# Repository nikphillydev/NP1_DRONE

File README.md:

# NP1 DRONE
I am attempting to build a quadcopter from scratch, both the PCB hardware (using KiCAD) and software (C/C++ on STM32).

I am a computer software engineering student at the University of Alberta. I started this project in early 2024 to push myself with embedded systems. Since its inception, I have learned a ton about PCB design and FreeRTOS firmware on STM32 microcontrollers. 

Everything I make in this project is from scratch. The STM32-based circuit boards are designed with KiCAD and ordered from JLCPCB with assembly. I am using FreeRTOS for the software because of its scalability in complex embedded projects. I have written all the device drivers from scratch, and wholly designed the multi-threaded architecture for each of the drone's sub-systems.

Each sub-system presents its own set of challenges. As an overview, there are 3 sub-systems of the NP1 Drone:
```
                     (Over-The-Air Messaging)                               (CANBUS)
[RC CONTROLLER]   <---------------------------->  [Flight Controller]   <--------------->  [Electronic Speed Controller] x4
```
#### 1. Flight Controller Overview
The Flight Controller (FCC) is a custom PCB design whose software runs the control system for the drone. In order to achieve this, it must 1) receive pilot input from the RC Controller, and 2) estimate its attitude and heading (roll, pitch, yaw). These inputs enter the onboard PID controller in order to calculate the necessary motor commands to send to the Electronic Speed Controllers (ESCs).

The FCC is equipped with a multitude of sensors, namely an IMU, magnetometer, barometer, optical flow sensor, and range finder. It performs sensor fusion through the use of an Extended Kalman Filter (EKF) and a few other custom algorithms. When it receives Over-The-Air (OTA) messages from the RC Controller, it monitors for a HEARTBEAT signal to detect LOSS-OF-LINK and perform flight termination. The control system interprets pilot input and sets the target roll, pitch, and yaw accordingly depending on flight mode (various flight modes still WIP).

<p align="center">
  <br>
  <sub><b>Figure 1:</b> The Flight Controller (FCC) sitting on a Lego frame. The USB powers the board and enables logging to my laptop; jumper wires connect the external range finder and optical flow sensor; the green and yellow twisted pair connect to the ESCs using CANBUS.</sub>
</p>

#### 2. RC Controller Overview
The RC Controller is simple: receive pilot input from various joysticks and buttons and send those values Over-The-Air (OTA) to the FCC. A custom OTA messaging protocol (modelled after MAVLINK) has been developed to facilitate this communication. The physical inputs of the RC Controller are fairly WIP right now. Currently, its a breadboard with push-buttons and a potentiometer, (hopefully) soon it will be a PS4 controller.

<p align="center">
  <br>
  <sub><b>Figure 2:</b> The RC Controller, in its current state. Spare hardware is used to capture pilot input.</sub>
</p>

#### 3. Electronic Speed Controller Overview
The Electronic Speed Controller (ESC) requires a strong understanding of Brushless DC (BLDC) motor control. The custom PCB design and software are designed around the (sensorless) 6-Step Trapezoidal control method, where a Back Electromotive Force (BEMF) measurement from the floating motor phase is measured in order to know when to switch the commutation to the next step. In order to perform proper closed-loop control in this method, the motor must be spinning fast enough to generate a sufficient BEMF. I designed the ESC to operate in a software defined state-machine. Here are the states:
1. STAND-BY: ESC is not commanding a rotation of the motor.
2. ARMING: Align-and-Go Step. ESC commands an open-loop ramp up of the motor to obtain sufficient BEMF measurements. Lasts for about 0.8 sec.
3. ARMED: ESC is commanding true closed-loop, 6-Step commutation with BEMF zero-crossing detection.

The ESC receives ARM, DISARM, and THROTTLE CANBUS messages from the FCC to transition between its internal states and increase / decrease motor RPM.

<table align="center">
  <tr>
    <td align="center" valign="top">
      <br>
      <sub><b>Figure 2:</b> The Electronic Speed Controller (ESC), connected to the FCC via CANBUS.</sub>
    </td>
    <td align="center" valign="top">
      <br>
      <sub><b>Figure 3:</b> The motor test stand; an ESC and BLDC motor mounted onto a wooden lever.</sub>
    </td>
  </tr>
</table>

### System Demo
This demo showcases the RC Controller sending my input Over-The-Air (OTA) to the FCC. The FCC receives these commands and uses its estimated state to calculate motor commands in its control system. The resulting commands are sent via CANBUS to the ESC on the motor test stand, controlling the BLDC motor.

https://github.com/user-attachments/assets/3e73fd2b-c005-44b4-9096-01581734d467

### In-Depth Design
For more detailed design, please see the hardware and software folders.

Here is the [hardware overview](hardware/README.md).

Here is the [software overview](software/STM32/README.md).

### A Note on the Use of AI
When I started the project in 2024, zero AI was used. Now, from 2026 onward, AI is obviously much better. However, this is a PASSION PROJECT. The goal of this project is to LEARN. I will not be able to effectively achieve that goal if I use AI. The intelligence you gain from AI is artificial. Therefore, I write all the code MYSELF. If there are bugs or I want some review / feedback of my work, I will use AI to do so. In this way, AI is the reviewer and I formulate my own thoughts first.

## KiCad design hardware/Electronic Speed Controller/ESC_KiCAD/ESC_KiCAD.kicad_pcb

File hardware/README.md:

## Hardware Overview
This project includes 2 custom PCB designs: 
1. Flight Control Computer (FCC)
2. Electronic Speed Controller (ESC)

#### PCB: Flight Control Computer [COMPLETE]
The FCC PCB incorporates:
- STM32G474 microcontroller
- BMI088 IMU (accelerometer + gyroscope), LIS3MDL magnetometer, BMP388 barometer
- USB 2.0 Full Speed (Data + Power)
- 2 SN65HVD232 CANbus transceivers (one bus for ESC comms and another bus for serial payloads)
- CC2500 2.4GHz RF transceiver (for comms with ground station)
- M24C32 32kBit EEPROM
- Power regulation (4S / 6S LIPO -> +5V -> +3.3V)
- Payload header (exposing +5V, +3.3V, GPIO, I2C, SPI, UART)

#### PCB: Electronic Speed Controller [COMPLETE]
The ESC PCB incorporates:
- STM32G474 microcontroller
- 3 Half-bridge MOSFET gate drivers to support a 3 phase BLDC motor
- 6 N-channel power MOSFETS (in 3 half-bridge topologies)
- Per phase voltage measurement
- Back-EMF zero-crossing detection (using MCU comparators)
- CANbus transceiver (comms to FCC)
- Power regulation (4S / 6S LIPO -> +11V -> +5V -> +3.3V)

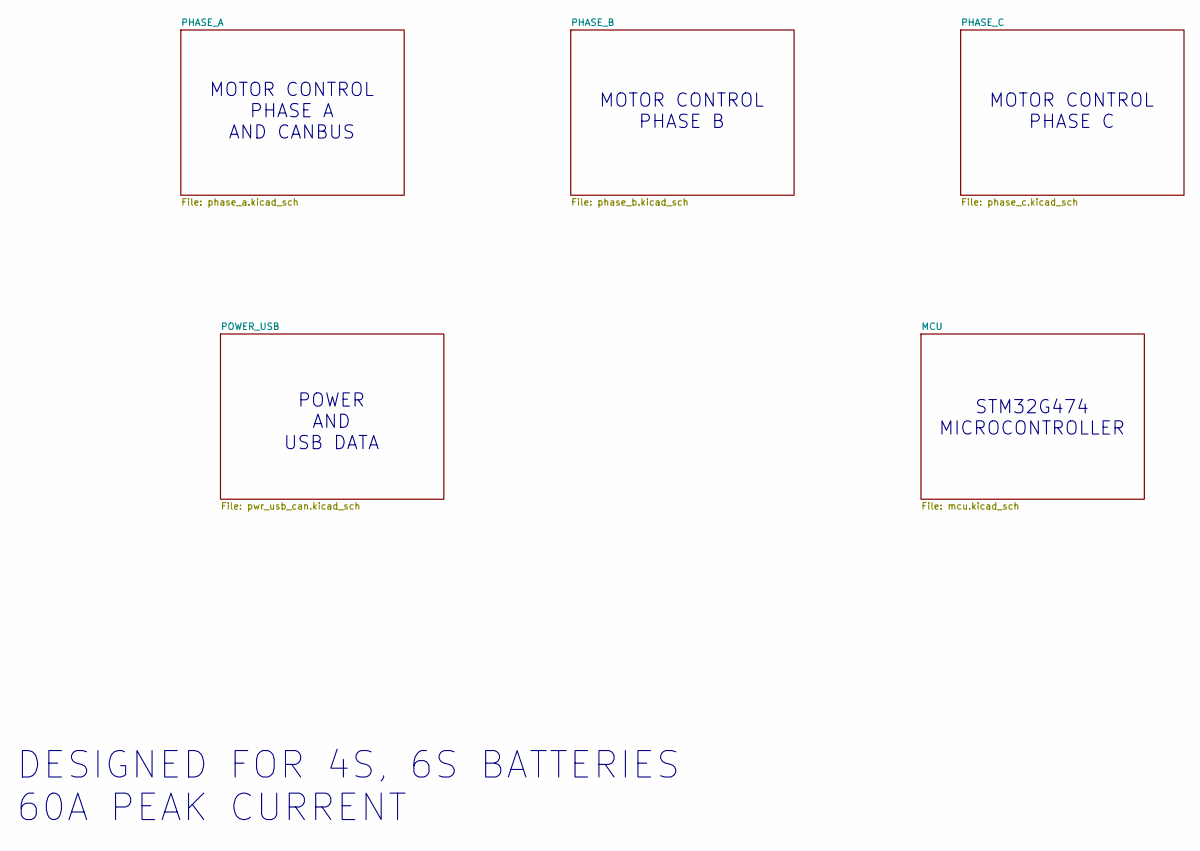
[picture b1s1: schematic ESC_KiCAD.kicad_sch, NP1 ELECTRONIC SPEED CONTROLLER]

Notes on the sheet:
MOTOR CONTROL PHASE C
POWER AND USB DATA
STM32G474 MICROCONTROLLER
MOTOR CONTROL PHASE B
DESIGNED FOR 4S, 6S BATTERIES 60A PEAK CURRENT
MOTOR CONTROL PHASE A AND CANBUS

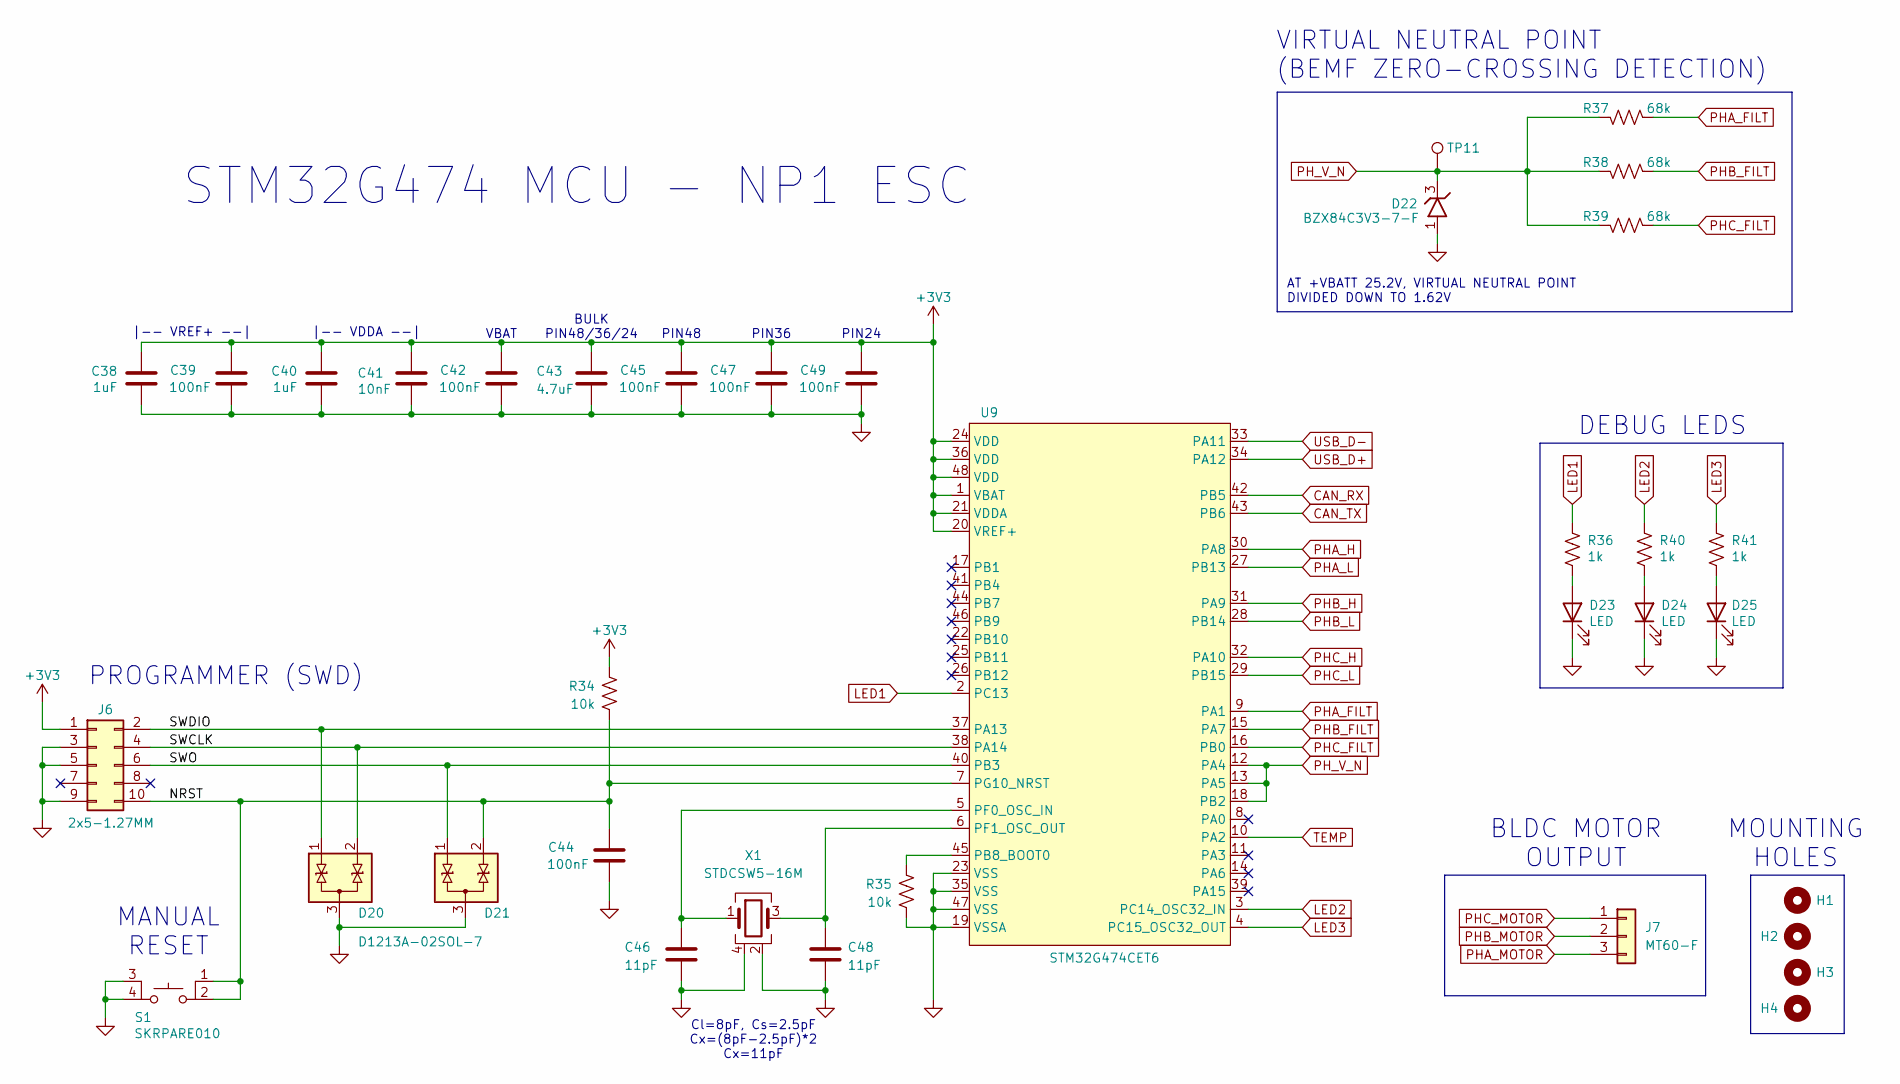
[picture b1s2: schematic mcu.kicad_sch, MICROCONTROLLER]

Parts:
C38, C40: 1uF; CAP_0805_2012Metric; Manufacturer Part # CL21B105KBFNNNE; JLCPCB Part # C28323
C39, C42, C44, C45, C47, C49: 100nF; CAP_0603_1608Metric; Manufacturer Part # CC0603KRX7R9BB104; JLCPCB Part # C14663
C41: 10nF; CAP_0603_1608Metric; Manufacturer Part # CL10B103KB8NNNC; JLCPCB Part # C57112
C43: 4.7uF; CAP_0805_2012Metric; Manufacturer Part # CL21A475KAQNNNE; JLCPCB Part # C1779
C46, C48: 11pF; CAP_0402_1005Metric; Manufacturer Part # GCM1555C1H110JA16D; JLCPCB Part # C710643
D20, D21: D1213A-02SOL-7; DiodesINC_SOT23-3; Manufacturer Part # D1213A-02SOL-7; JLCPCB Part # C460585
D22: BZX84C3V3-7-F; DiodesINC_SOT23-3; Manufacturer Part # BZX84C3V3-7-F; JLCPCB Part # C177019
D23, D24, D25: LED; LED_0603_1608Metric; Manufacturer Part # EAST16086YA4; JLCPCB Part # C72038
H1, H2, H3, H4: MountingHole; MountingHole_3.2mm_M3_ISO7380_Pad
J6: 2x5-1.27MM; CONN_MALE_SMT_1.27MM_2x5; Manufacturer Part # 20021121-00010C4LF; JLCPCB Part # C150517
J7: MT60-F; CONN_MALE_TH_MT60; Manufacturer Part # MT60-F; JLCPCB Part # C40020701
R34, R35: 10k; RES_0603_1608Metric; Manufacturer Part # RMCF0603FT10K0; JLCPCB Part # C25804
R36, R40, R41: 1k; RES_0603_1608Metric; Manufacturer Part # RMCF0603FT1K00; JLCPCB Part # C21190
R37, R38, R39: 68k; RES_0603_1608Metric; Manufacturer Part # ERJ-3EKF6802V; JLCPCB Part # C23231
S1: SKRPARE010; TACT_SKRP; Manufacturer Part # SKRPARE010; JLCPCB Part # C341730
TP11: TestPoint; TestPoint_THTPad_D2.5mm_Drill1.2mm
U9: STM32G474CET6; STM_LQFP48; Manufacturer Part # STM32G474CET6; JLCPCB Part # C730125
X1: STDCSW5-16M; NDK_NX2520SA; Manufacturer Part # STDCSW5-16M; JLCPCB Part # C280836

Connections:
+3V3: C38.2, C39.2, C40.2, C41.2, C42.2, C43.1, C45.2, C47.2, C49.2, J6.1, R34.1, U9.1 (VBAT), U9.20 (VREF+), U9.21 (VDDA), U9.24 (VDD), U9.36 (VDD), U9.48 (VDD); also elsewhere on the board
/MCU/NRST: C44.2, D21.2 (K), J6.10, R34.2, S1.1, S1.2, U9.7 (PG10_NRST)
/MCU/SWCLK: D20.2 (K), J6.4, U9.38 (PA14)
/MCU/SWDIO: D20.1 (K), J6.2, U9.37 (PA13)
/MCU/SWO: D21.1 (K), J6.6, U9.40 (PB3)
CAN_RX: U9.42 (PB5); also elsewhere on the board
CAN_TX: U9.43 (PB6); also elsewhere on the board
GND: C38.1, C39.1, C40.1, C41.1, C42.1, C43.2, C44.1, C45.1, C46.2, C47.1, C48.2, C49.1, D20.3 (A), D21.3 (A), D22.1 (A), D23.1 (K), D24.1 (K), D25.1 (K), J6.3, J6.5, J6.9, R35.2, S1.3, S1.4, U9.19 (VSSA), U9.23 (VSS), U9.35 (VSS), U9.47 (VSS), X1.2, X1.4; also elsewhere on the board
LED1: R36.1, U9.2 (PC13)
LED2: R40.1, U9.3 (PC14_OSC32_IN)
LED3: R41.1, U9.4 (PC15_OSC32_OUT)
unnamed: D23.2 (A), R36.2
unnamed: D24.2 (A), R40.2
unnamed: D25.2 (A), R41.2
unnamed: R35.1, U9.45 (PB8_BOOT0)
unnamed: C46.1, U9.5 (PF0_OSC_IN), X1.1
unnamed: C48.1, U9.6 (PF1_OSC_OUT), X1.3
PHA_FILT: R37.2, U9.9 (PA1); also elsewhere on the board
PHA_H: U9.30 (PA8); also elsewhere on the board
PHA_L: U9.27 (PB13); also elsewhere on the board
PHA_MOTOR: J7.3; also elsewhere on the board
PHB_FILT: R38.2, U9.15 (PA7); also elsewhere on the board
PHB_H: U9.31 (PA9); also elsewhere on the board
PHB_L: U9.28 (PB14); also elsewhere on the board
PHB_MOTOR: J7.2; also elsewhere on the board
PHC_FILT: R39.2, U9.16 (PB0); also elsewhere on the board
PHC_H: U9.32 (PA10); also elsewhere on the board
PHC_L: U9.29 (PB15); also elsewhere on the board
PHC_MOTOR: J7.1; also elsewhere on the board
PH_V_N: D22.3 (K), R37.1, R38.1, R39.1, TP11.1, U9.12 (PA4), U9.13 (PA5), U9.18 (PB2)
TEMP: U9.10 (PA2); also elsewhere on the board
USB_D+: U9.34 (PA12); also elsewhere on the board
USB_D-: U9.33 (PA11); also elsewhere on the board

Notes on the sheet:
MANUAL RESET
MOUNTING HOLES
BULK PIN48/36/24
VIRTUAL NEUTRAL POINT (BEMF ZERO-CROSSING DETECTION)
VBAT
Cl=8pF, Cs=2.5pF Cx=(8pF-2.5pF)*2 Cx=11pF
AT +VBATT 25.2V, VIRTUAL NEUTRAL POINT DIVIDED DOWN TO 1.62V
PIN24
PIN36
DEBUG LEDS
PROGRAMMER (SWD)
BLDC MOTOR OUTPUT
|-- VREF+ --|
STM32G474 MCU - NP1 ESC
|-- VDDA --|
PIN48

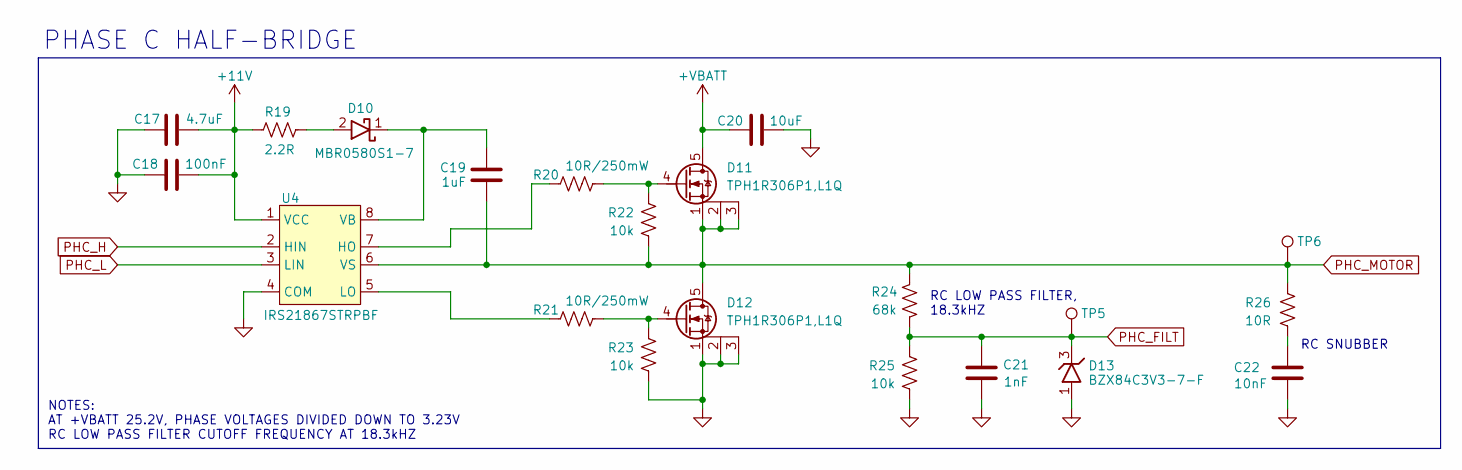
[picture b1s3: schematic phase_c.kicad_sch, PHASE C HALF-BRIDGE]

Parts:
C17: 4.7uF; CAP_0805_2012Metric; Manufacturer Part # CL21A475KAQNNNE; JLCPCB Part # C1779
C18: 100nF; CAP_0603_1608Metric; Manufacturer Part # CC0603KRX7R9BB104; JLCPCB Part # C14663
C19: 1uF; CAP_0805_2012Metric; Manufacturer Part # CL21B105KBFNNNE; JLCPCB Part # C28323
C20: 10uF; CAP_1206_3216Metric; Manufacturer Part # CL31A106KBHNNNE; JLCPCB Part # C13585
C21: 1nF; CAP_0603_1608Metric; Manufacturer Part # CL10B102KB8NNNC; JLCPCB Part # C1588
C22: 10nF; CAP_0603_1608Metric; Manufacturer Part # CL10B103KB8NNNC; JLCPCB Part # C57112
D10: MBR0580S1-7; DiodesINC_SOD123; Manufacturer Part # MBR0580S1-7; JLCPCB Part # C177047
D11, D12: TPH1R306P1,L1Q; PQFN-8-EP_6x5mm_P1.27mm_Generic; Manufacturer Part # TPH1R306P1,L1Q; JLCPCB Part # C6290261
D13: BZX84C3V3-7-F; DiodesINC_SOT23-3; Manufacturer Part # BZX84C3V3-7-F; JLCPCB Part # C177019
R19: 2.2R; RES_1206_3216Metric; Manufacturer Part # CRCW12062R20FKEAHP; JLCPCB Part # C1854860
R20, R21: 10R/250mW; RES_0805_2012Metric; Manufacturer Part # AC0805FR-7W10RL; JLCPCB Part # C727983
R22, R23, R25: 10k; RES_0603_1608Metric; Manufacturer Part # RMCF0603FT10K0; JLCPCB Part # C25804
R24: 68k; RES_0603_1608Metric; Manufacturer Part # ERJ-3EKF6802V; JLCPCB Part # C23231
R26: 10R; RES_0603_1608Metric; Manufacturer Part # RC0603FR-0710RL; JLCPCB Part # C22859
TP5, TP6: TestPoint; TestPoint_THTPad_D2.5mm_Drill1.2mm
U4: IRS21867STRPBF; SOIC-8; Manufacturer Part # IRS21867STRPBF; JLCPCB Part # C52290

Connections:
+11V: C17.2, C18.2, R19.1, U4.1 (VCC); also elsewhere on the board
+VBATT: C20.1, D11.5 (D); also elsewhere on the board
GND: C17.1, C18.1, C20.2, C21.1, C22.1, D12.1 (S), D12.2 (S), D12.3 (S), D13.1 (A), R23.2, R25.2, U4.4 (COM); also elsewhere on the board
unnamed: C22.2, R26.2
unnamed: D10.2 (A), R19.2
unnamed: C19.2, D10.1 (K), U4.8 (VB)
unnamed: D11.4 (G), R20.2, R22.1
unnamed: D12.4 (G), R21.2, R23.1
unnamed: R20.1, U4.7 (HO)
unnamed: R21.1, U4.5 (LO)
PHC_FILT: C21.2, D13.3 (K), R24.1, R25.1, TP5.1; also elsewhere on the board
PHC_H: U4.2 (HIN); also elsewhere on the board
PHC_L: U4.3 (LIN); also elsewhere on the board
PHC_MOTOR: C19.1, D11.1 (S), D11.2 (S), D11.3 (S), D12.5 (D), R22.2, R24.2, R26.1, TP6.1, U4.6 (VS); also elsewhere on the board

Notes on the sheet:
RC SNUBBER
NOTES: AT +VBATT 25.2V, PHASE VOLTAGES DIVIDED DOWN TO 3.23V RC LOW PASS FILTER CUTOFF FREQUENCY AT 18.3kHZ
RC LOW PASS FILTER, 18.3kHZ
PHASE C HALF-BRIDGE

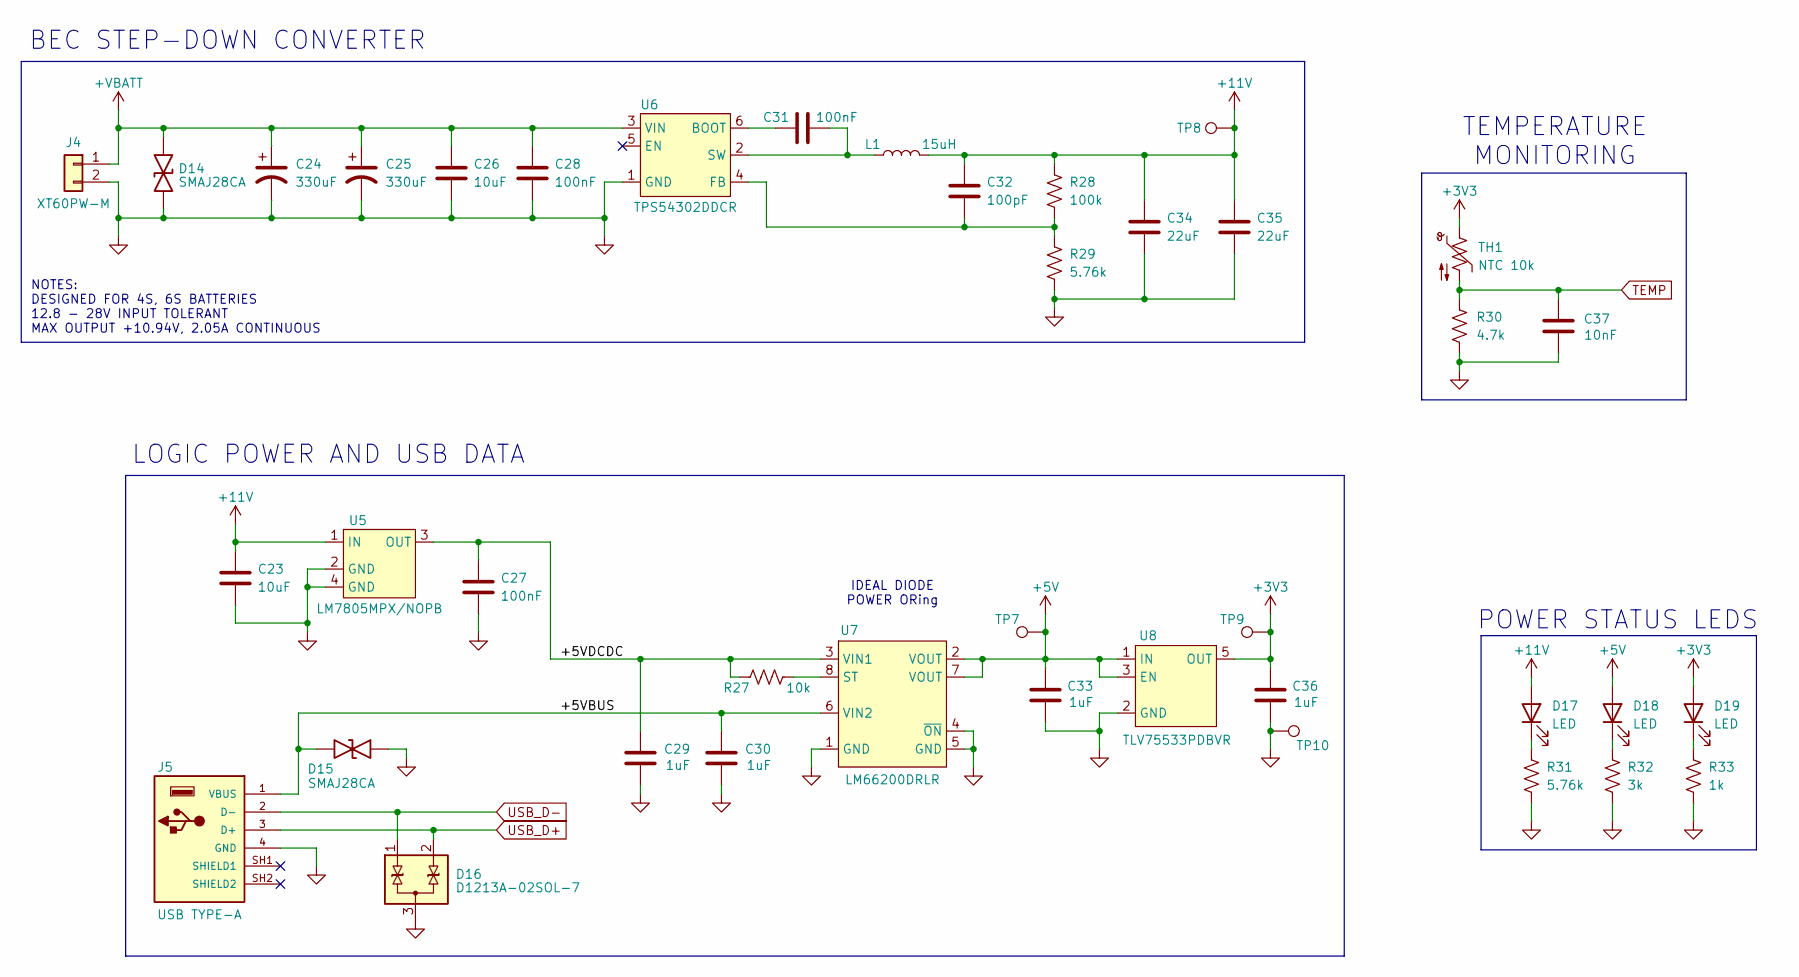
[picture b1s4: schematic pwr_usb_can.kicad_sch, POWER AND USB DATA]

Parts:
C23, C26: 10uF; CAP_1206_3216Metric; Manufacturer Part # CL31A106KBHNNNE; JLCPCB Part # C13585
C24, C25: 330uF; CAP_ALUM_HORIZONTAL; Manufacturer Part # 35ZLH330MEFC10X12.5; JLCPCB Part # C75177
C27, C28, C31: 100nF; CAP_0603_1608Metric; Manufacturer Part # CC0603KRX7R9BB104; JLCPCB Part # C14663
C29, C30, C33, C36: 1uF; CAP_0805_2012Metric; Manufacturer Part # CL21B105KBFNNNE; JLCPCB Part # C28323
C32: 100pF; CAP_0603_1608Metric; Manufacturer Part # CL10C101JB8NNNC; JLCPCB Part # C14858
C34, C35: 22uF; CAP_0805_2012Metric; Manufacturer Part # CL21A226MAYNNNE; JLCPCB Part # C45783
C37: 10nF; CAP_0603_1608Metric; Manufacturer Part # CL10B103KB8NNNC; JLCPCB Part # C57112
D14, D15: SMAJ28CA; Littelfuse_SMA; Manufacturer Part # SMAJ28CA; JLCPCB Part # C148228
D16: D1213A-02SOL-7; DiodesINC_SOT23-3; Manufacturer Part # D1213A-02SOL-7; JLCPCB Part # C460585
D17, D18, D19: LED; LED_0603_1608Metric; Manufacturer Part # EAST16086YA4; JLCPCB Part # C72038
J4: XT60PW-M; CONN_MALE_TH_XT60PW; Manufacturer Part # XT60PW-M; JLCPCB Part # C98732
J5: USB TYPE-A; USB2.0_4P_AMPHENOL_87583-2010BLF; Manufacturer Part # 87583-2010BLF; JLCPCB Part # C599118
L1: 15uH; L_6045S; Manufacturer Part # SWPA6045S150MT; JLCPCB Part # C83374
R27: 10k; RES_0603_1608Metric; Manufacturer Part # RMCF0603FT10K0; JLCPCB Part # C25804
R28: 100k; RES_0603_1608Metric; Manufacturer Part # RC0603FR-07100KL; JLCPCB Part # C25803
R29, R31: 5.76k; RES_0603_1608Metric; Manufacturer Part # RC0603FR-075K76L; JLCPCB Part # C2933239
R30: 4.7k; RES_0603_1608Metric; Manufacturer Part # RC0603FR-074K7L; JLCPCB Part # C23162
R32: 3k; RES_0603_1608Metric; Manufacturer Part # RMCF0603FT3K00; JLCPCB Part # C4211
R33: 1k; RES_0603_1608Metric; Manufacturer Part # RMCF0603FT1K00; JLCPCB Part # C21190
TH1: NTC 10k; RES_0603_1608Metric; Manufacturer Part # NCU18XH103F60RB; JLCPCB Part # C440252
TP7, TP8, TP9, TP10: TestPoint; TestPoint_Pad_2.0x2.0mm
U5: LM7805MPX/NOPB; TI_SOT223-4; Manufacturer Part # LM7805MPX/NOPB; JLCPCB Part # C2848241
U6: TPS54302DDCR; TI_SOT23-6; Manufacturer Part # TPS54302DDCR; JLCPCB Part # C311983
U7: LM66200DRLR; TI_SOT-5X3; Manufacturer Part # LM66200DRLR; JLCPCB Part # C3235556
U8: TLV75533PDBVR; TI_SOT23-5; Manufacturer Part # TLV75533PDBVR; JLCPCB Part # C404027

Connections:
+3V3: C36.2, D19.2 (A), TH1.1, TP9.1, U8.5 (OUT); also elsewhere on the board
+5V: C33.2, D18.2 (A), TP7.1, U7.2 (VOUT), U7.7 (VOUT), U8.1 (IN), U8.3 (EN)
+11V: C23.1, C32.1, C34.1, C35.1, D17.2 (A), L1.2, R28.1, TP8.1, U5.1 (IN); also elsewhere on the board
+VBATT: C24.1, C25.1, C26.1, C28.2, D14.1 (K), J4.1, U6.3 (VIN); also elsewhere on the board
/POWER_USB/+5VBUS: C30.2, D15.1 (K), J5.1 (VBUS), U7.6 (VIN2)
/POWER_USB/+5VDCDC: C27.2, C29.2, R27.1, U5.3 (OUT), U7.3 (VIN1)
GND: C23.2, C24.2, C25.2, C26.2, C27.1, C28.1, C29.1, C30.1, C33.1, C34.2, C35.2, C36.1, C37.1, D14.2 (A), D15.2 (A), D16.3 (A), J4.2, J5.4 (GND), R29.2, R30.2, R31.2, R32.2, R33.2, TP10.1, U5.2 (GND), U5.4 (GND), U6.1 (GND), U7.1 (GND), U7.4 (~ON), U7.5 (GND), U8.2 (GND); also elsewhere on the board
unnamed: D17.1 (K), R31.1
unnamed: D18.1 (K), R32.1
unnamed: D19.1 (K), R33.1
unnamed: C31.1, U6.6 (BOOT)
unnamed: C32.2, R28.2, R29.1, U6.4 (FB)
unnamed: C31.2, L1.1, U6.2 (SW)
unnamed: R27.2, U7.8 (ST)
TEMP: C37.2, R30.1, TH1.2; also elsewhere on the board
USB_D+: D16.2 (K), J5.3 (D+); also elsewhere on the board
USB_D-: D16.1 (K), J5.2 (D-); also elsewhere on the board

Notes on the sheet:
POWER STATUS LEDS
LOGIC POWER AND USB DATA
IDEAL DIODE POWER ORing
TEMPERATURE MONITORING
NOTES: DESIGNED FOR 4S, 6S BATTERIES 12.8 - 28V INPUT TOLERANT MAX OUTPUT +10.94V, 2.05A CONTINUOUS
BEC STEP-DOWN CONVERTER

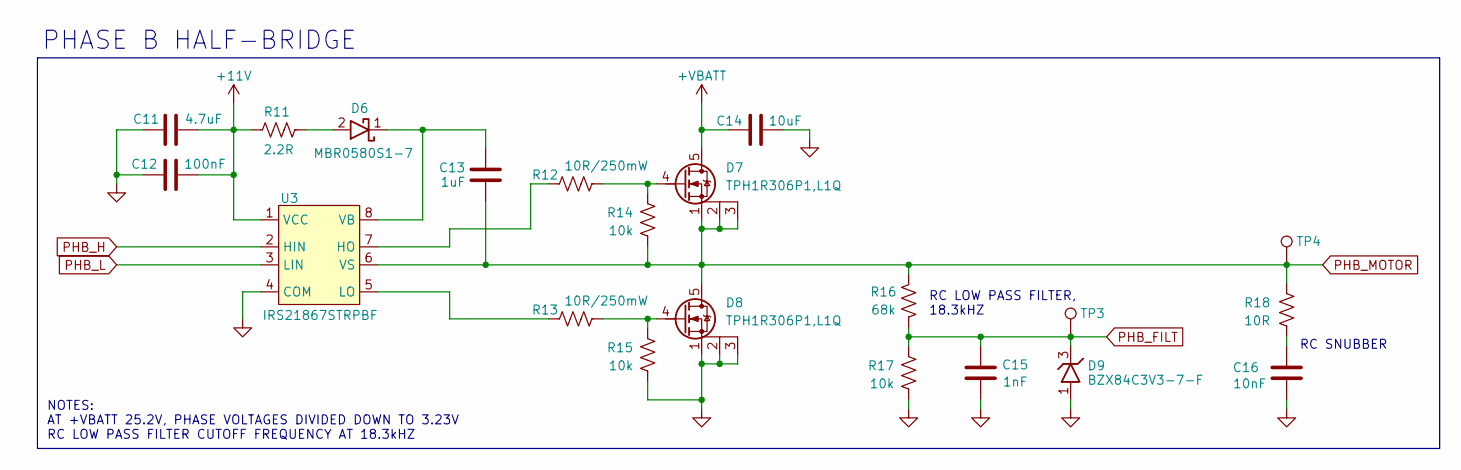
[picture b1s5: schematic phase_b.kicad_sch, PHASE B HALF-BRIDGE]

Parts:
C11: 4.7uF; CAP_0805_2012Metric; Manufacturer Part # CL21A475KAQNNNE; JLCPCB Part # C1779
C12: 100nF; CAP_0603_1608Metric; Manufacturer Part # CC0603KRX7R9BB104; JLCPCB Part # C14663
C13: 1uF; CAP_0805_2012Metric; Manufacturer Part # CL21B105KBFNNNE; JLCPCB Part # C28323
C14: 10uF; CAP_1206_3216Metric; Manufacturer Part # CL31A106KBHNNNE; JLCPCB Part # C13585
C15: 1nF; CAP_0603_1608Metric; Manufacturer Part # CL10B102KB8NNNC; JLCPCB Part # C1588
C16: 10nF; CAP_0603_1608Metric; Manufacturer Part # CL10B103KB8NNNC; JLCPCB Part # C57112
D6: MBR0580S1-7; DiodesINC_SOD123; Manufacturer Part # MBR0580S1-7; JLCPCB Part # C177047
D7, D8: TPH1R306P1,L1Q; PQFN-8-EP_6x5mm_P1.27mm_Generic; Manufacturer Part # TPH1R306P1,L1Q; JLCPCB Part # C6290261
D9: BZX84C3V3-7-F; DiodesINC_SOT23-3; Manufacturer Part # BZX84C3V3-7-F; JLCPCB Part # C177019
R11: 2.2R; RES_1206_3216Metric; Manufacturer Part # CRCW12062R20FKEAHP; JLCPCB Part # C1854860
R12, R13: 10R/250mW; RES_0805_2012Metric; Manufacturer Part # AC0805FR-7W10RL; JLCPCB Part # C727983
R14, R15, R17: 10k; RES_0603_1608Metric; Manufacturer Part # RMCF0603FT10K0; JLCPCB Part # C25804
R16: 68k; RES_0603_1608Metric; Manufacturer Part # ERJ-3EKF6802V; JLCPCB Part # C23231
R18: 10R; RES_0603_1608Metric; Manufacturer Part # RC0603FR-0710RL; JLCPCB Part # C22859
TP3, TP4: TestPoint; TestPoint_THTPad_D2.5mm_Drill1.2mm
U3: IRS21867STRPBF; SOIC-8; Manufacturer Part # IRS21867STRPBF; JLCPCB Part # C52290

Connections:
+11V: C11.2, C12.2, R11.1, U3.1 (VCC); also elsewhere on the board
+VBATT: C14.1, D7.5 (D); also elsewhere on the board
GND: C11.1, C12.1, C14.2, C15.1, C16.1, D8.1 (S), D8.2 (S), D8.3 (S), D9.1 (A), R15.2, R17.2, U3.4 (COM); also elsewhere on the board
unnamed: C16.2, R18.2
unnamed: D6.2 (A), R11.2
unnamed: C13.2, D6.1 (K), U3.8 (VB)
unnamed: D7.4 (G), R12.2, R14.1
unnamed: D8.4 (G), R13.2, R15.1
unnamed: R12.1, U3.7 (HO)
unnamed: R13.1, U3.5 (LO)
PHB_FILT: C15.2, D9.3 (K), R16.1, R17.1, TP3.1; also elsewhere on the board
PHB_H: U3.2 (HIN); also elsewhere on the board
PHB_L: U3.3 (LIN); also elsewhere on the board
PHB_MOTOR: C13.1, D7.1 (S), D7.2 (S), D7.3 (S), D8.5 (D), R14.2, R16.2, R18.1, TP4.1, U3.6 (VS); also elsewhere on the board

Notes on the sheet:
RC LOW PASS FILTER, 18.3kHZ
RC SNUBBER
NOTES: AT +VBATT 25.2V, PHASE VOLTAGES DIVIDED DOWN TO 3.23V RC LOW PASS FILTER CUTOFF FREQUENCY AT 18.3kHZ
PHASE B HALF-BRIDGE

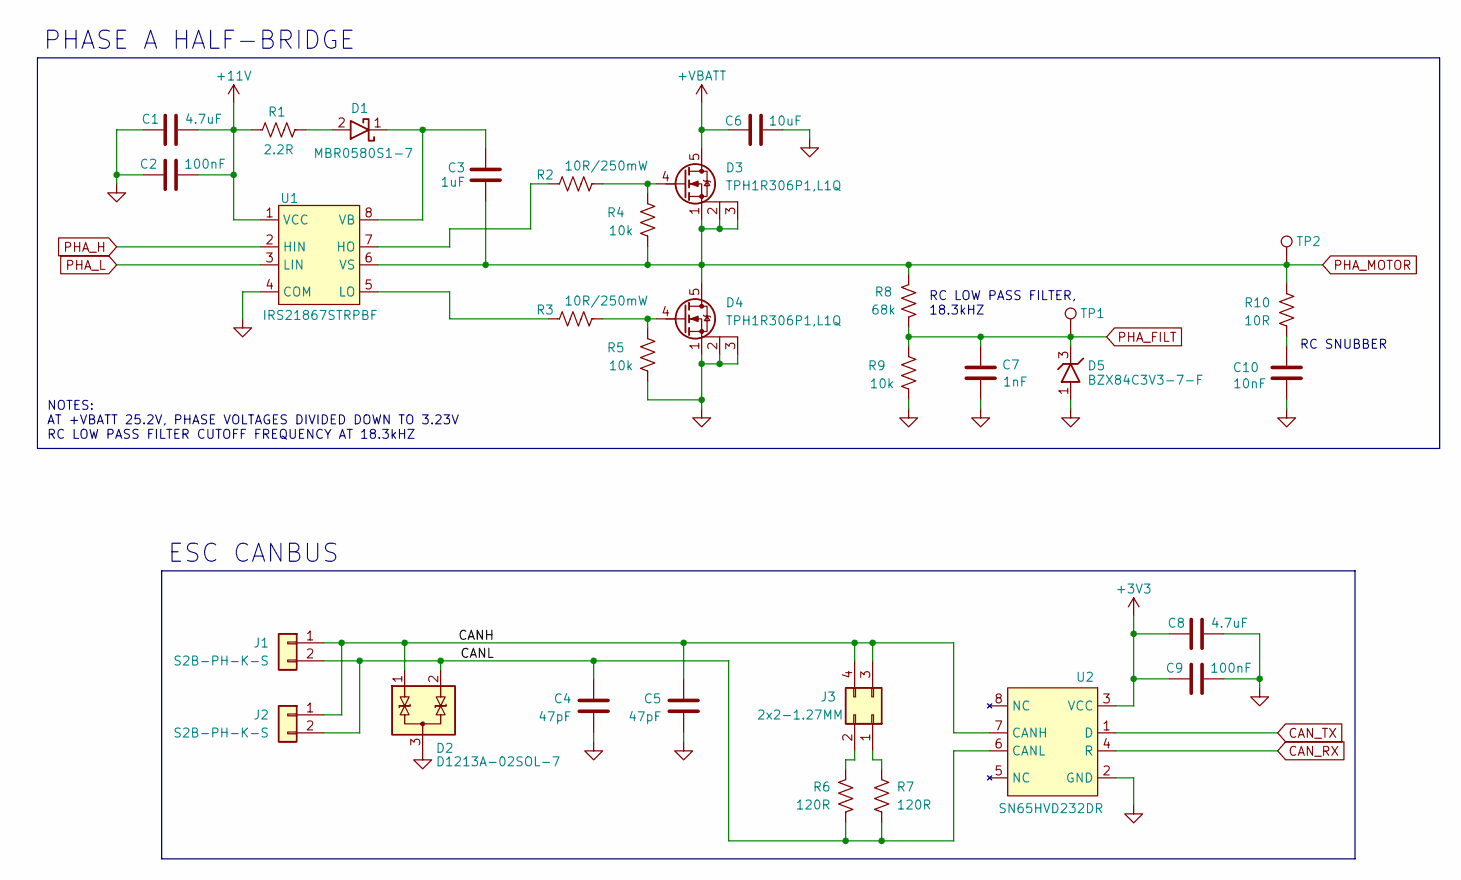
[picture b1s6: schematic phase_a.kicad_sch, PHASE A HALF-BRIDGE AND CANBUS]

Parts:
C1, C8: 4.7uF; CAP_0805_2012Metric; Manufacturer Part # CL21A475KAQNNNE; JLCPCB Part # C1779
C2, C9: 100nF; CAP_0603_1608Metric; Manufacturer Part # CC0603KRX7R9BB104; JLCPCB Part # C14663
C3: 1uF; CAP_0805_2012Metric; Manufacturer Part # CL21B105KBFNNNE; JLCPCB Part # C28323
C4, C5: 47pF; CAP_0603_1608Metric; Manufacturer Part # CL10C470JB8NNNC; JLCPCB Part # C1671
C6: 10uF; CAP_1206_3216Metric; Manufacturer Part # CL31A106KBHNNNE; JLCPCB Part # C13585
C7: 1nF; CAP_0603_1608Metric; Manufacturer Part # CL10B102KB8NNNC; JLCPCB Part # C1588
C10: 10nF; CAP_0603_1608Metric; Manufacturer Part # CL10B103KB8NNNC; JLCPCB Part # C57112
D1: MBR0580S1-7; DiodesINC_SOD123; Manufacturer Part # MBR0580S1-7; JLCPCB Part # C177047
D2: D1213A-02SOL-7; DiodesINC_SOT23-3; Manufacturer Part # D1213A-02SOL-7; JLCPCB Part # C460585
D3, D4: TPH1R306P1,L1Q; PQFN-8-EP_6x5mm_P1.27mm_Generic; Manufacturer Part # TPH1R306P1,L1Q; JLCPCB Part # C6290261
D5: BZX84C3V3-7-F; DiodesINC_SOT23-3; Manufacturer Part # BZX84C3V3-7-F; JLCPCB Part # C177019
J1, J2: S2B-PH-K-S; CONN_JST_S2B-PH-K-S; Manufacturer Part # S2B-PH-K-S; JLCPCB Part # C173752
J3: 2x2-1.27MM; CONN_MALE_TH_1.27MM_2x2; Manufacturer Part # GRPB022VWVN-RC; JLCPCB Part # C18197867
R1: 2.2R; RES_1206_3216Metric; Manufacturer Part # CRCW12062R20FKEAHP; JLCPCB Part # C1854860
R2, R3: 10R/250mW; RES_0805_2012Metric; Manufacturer Part # AC0805FR-7W10RL; JLCPCB Part # C727983
R4, R5, R9: 10k; RES_0603_1608Metric; Manufacturer Part # RMCF0603FT10K0; JLCPCB Part # C25804
R6, R7: 120R; RES_0603_1608Metric; Manufacturer Part # RC0603FR-07120RL; JLCPCB Part # C22787
R8: 68k; RES_0603_1608Metric; Manufacturer Part # ERJ-3EKF6802V; JLCPCB Part # C23231
R10: 10R; RES_0603_1608Metric; Manufacturer Part # RC0603FR-0710RL; JLCPCB Part # C22859
TP1, TP2: TestPoint; TestPoint_THTPad_D2.5mm_Drill1.2mm
U1: IRS21867STRPBF; SOIC-8; Manufacturer Part # IRS21867STRPBF; JLCPCB Part # C52290
U2: SN65HVD232DR; SOIC-8; Manufacturer Part # SN65HVD232DR; JLCPCB Part # C30530

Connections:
+3V3: C8.1, C9.1, U2.3 (VCC); also elsewhere on the board
+11V: C1.2, C2.2, R1.1, U1.1 (VCC); also elsewhere on the board
+VBATT: C6.1, D3.5 (D); also elsewhere on the board
/PHASE_A/CANH: C5.1, D2.1 (K), J1.1, J2.1, J3.3, J3.4, U2.7 (CANH)
/PHASE_A/CANL: C4.1, D2.2 (K), J1.2, J2.2, R6.2, R7.2, U2.6 (CANL)
CAN_RX: U2.4 (R); also elsewhere on the board
CAN_TX: U2.1 (D); also elsewhere on the board
GND: C1.1, C2.1, C4.2, C5.2, C6.2, C7.1, C8.2, C9.2, C10.1, D2.3 (A), D4.1 (S), D4.2 (S), D4.3 (S), D5.1 (A), R5.2, R9.2, U1.4 (COM), U2.2 (GND); also elsewhere on the board
unnamed: C10.2, R10.2
unnamed: D1.2 (A), R1.2
unnamed: C3.2, D1.1 (K), U1.8 (VB)
unnamed: D3.4 (G), R2.2, R4.1
unnamed: D4.4 (G), R3.2, R5.1
unnamed: J3.1, R7.1
unnamed: J3.2, R6.1
unnamed: R2.1, U1.7 (HO)
unnamed: R3.1, U1.5 (LO)
PHA_FILT: C7.2, D5.3 (K), R8.1, R9.1, TP1.1; also elsewhere on the board
PHA_H: U1.2 (HIN); also elsewhere on the board
PHA_L: U1.3 (LIN); also elsewhere on the board
PHA_MOTOR: C3.1, D3.1 (S), D3.2 (S), D3.3 (S), D4.5 (D), R4.2, R8.2, R10.1, TP2.1, U1.6 (VS); also elsewhere on the board

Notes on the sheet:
RC LOW PASS FILTER, 18.3kHZ
PHASE A HALF-BRIDGE
ESC CANBUS
NOTES: AT +VBATT 25.2V, PHASE VOLTAGES DIVIDED DOWN TO 3.23V RC LOW PASS FILTER CUTOFF FREQUENCY AT 18.3kHZ
RC SNUBBER

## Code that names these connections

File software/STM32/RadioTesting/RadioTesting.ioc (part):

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Mcu.Name=STM32G474C(B-C-E)Tx
Mcu.Package=LQFP48
Mcu.UserName=STM32G474CETx
PA0.GPIOParameters=PinState,GPIO_PuPd,GPIO_Label
PA0.GPIO_Label=GYRO_CS
PA0.GPIO_PuPd=GPIO_PULLUP
PA0.PinState=GPIO_PIN_SET
PA0.Signal=GPIO_Output
PA1.GPIOParameters=GPIO_PuPd,GPIO_Label
PA1.GPIO_Label=GYRO_INT
PA1.GPIO_PuPd=GPIO_PULLDOWN
PA1.Signal=GPXTI1
PA10.GPIOParameters=PinState,GPIO_Label
PA10.GPIO_Label=GPIO6
PA10.PinState=GPIO_PIN_RESET
PA10.Signal=GPIO_Output
PA11.Mode=Device
PA11.Signal=USB_DM
PA12.Mode=Device
PA12.Signal=USB_DP
PA13.Mode=Trace_Asynchronous_SW
PA13.Signal=SYS_JTMS-SWDIO
PA14.Mode=Trace_Asynchronous_SW
PA14.Signal=SYS_JTCK-SWCLK
PA15.GPIOParameters=PinState,GPIO_Label
PA15.GPIO_Label=GPIO5
PA15.PinState=GPIO_PIN_SET
PA15.Signal=GPIO_Output
PA2.Mode=Asynchronous
PA2.Signal=USART2_TX
PA3.Mode=Asynchronous
PA3.Signal=USART2_RX
PA4.GPIOParameters=PinState,GPIO_PuPd,GPIO_Label
PA4.GPIO_Label=ACCEL_CS
PA4.GPIO_PuPd=GPIO_PULLUP
PA4.PinState=GPIO_PIN_SET
PA4.Signal=GPIO_Output
PA5.Mode=Full_Duplex_Master
PA5.Signal=SPI1_SCK
PA6.Mode=Full_Duplex_Master
PA6.Signal=SPI1_MISO
PA7.Mode=Full_Duplex_Master
PA7.Signal=SPI1_MOSI
PA8.Mode=I2C
PA8.Signal=I2C2_SDA
PA9.Mode=I2C
PA9.Signal=I2C2_SCL
PB0.GPIOParameters=GPIO_Label
PB0.GPIO_Label=CC2500_GDO0
PB0.Signal=GPIO_Input
PB1.GPIOParameters=PinState,GPIO_PuPd,GPIO_Label
PB1.GPIO_Label=CC2500_CS
PB1.GPIO_PuPd=GPIO_PULLUP
PB1.PinState=GPIO_PIN_SET
PB1.Signal=GPIO_Output
PB10.GPIOParameters=GPIO_Label
PB10.GPIO_Label=GPIO8
PB10.Signal=GPIO_Output
PB11.GPIOParameters=GPIO_Label
PB11.GPIO_Label=GPIO9
PB11.Signal=GPIO_Output
PB12.GPIOParameters=GPIO_PuPd,GPIO_Label
PB12.GPIO_Label=MAG_DRDY
PB12.GPIO_PuPd=GPIO_PULLDOWN
PB12.Signal=GPXTI12
PB13.GPIOParameters=GPIO_Label
PB13.GPIO_Label=MAG_INT
PB13.Signal=GPIO_Input
PB14.GPIOParameters=GPIO_PuPd,GPIO_Label
PB14.GPIO_Label=BMP_INT
PB14.GPIO_PuPd=GPIO_PULLDOWN
PB14.Signal=GPXTI14
PB15.GPIOParameters=GPIO_Label
PB15.GPIO_Label=GPIO7
PB15.Signal=GPIO_Output
PB2.GPIOParameters=GPIO_Label
PB2.GPIO_Label=CC2500_GDO2
PB2.Signal=GPIO_Input
PB3.Mode=Trace_Asynchronous_SW
PB3.Signal=SYS_JTDO-SWO
PB4.GPIOParameters=GPIO_Label
PB4.GPIO_Label=GPIO4
PB4.Signal=GPIO_Output
PB5.Mode=FDCAN_Activate
PB5.Signal=FDCAN2_RX
PB6.Mode=FDCAN_Activate
PB6.Signal=FDCAN2_TX
PB7.GPIOParameters=GPIO_Label
PB7.GPIO_Label=GPIO1
PB7.Signal=GPIO_Output
PB8-BOOT0.Mode=FDCAN_Activate
PB8-BOOT0.Signal=FDCAN1_RX
PB9.Mode=FDCAN_Activate
PB9.Signal=FDCAN1_TX
PC13.GPIOParameters=GPIO_Label
PC13.GPIO_Label=GPIO2
PC13.Signal=GPIO_Output
PC14-OSC32_IN.GPIOParameters=GPIO_Label
PC14-OSC32_IN.GPIO_Label=FLOW_CS
PC14-OSC32_IN.Signal=GPIO_Output
PC15-OSC32_OUT.GPIOParameters=GPIO_PuPd,GPIO_Label
PC15-OSC32_OUT.GPIO_Label=ACCEL_INT
PC15-OSC32_OUT.GPIO_PuPd=GPIO_PULLDOWN
PC15-OSC32_OUT.Signal=GPXTI15
PF0-OSC_IN.Mode=HSE-External-Oscillator
PF0-OSC_IN.Signal=RCC_OSC_IN
PF1-OSC_OUT.Mode=HSE-External-Oscillator
PF1-OSC_OUT.Signal=RCC_OSC_OUT
RCC.HSE_VALUE=16000000
RCC.SYSCLKFreq_VALUE=170000000
RCC.SYSCLKSource=RCC_SYSCLKSOURCE_PLLCLK
board=custom

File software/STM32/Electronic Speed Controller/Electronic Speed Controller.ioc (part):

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Mcu.Name=STM32G474C(B-C-E)Tx
Mcu.Package=LQFP48
Mcu.UserName=STM32G474CETx
PA1.GPIOParameters=GPIO_Label
PA1.GPIO_Label=PHA_FILT
PA1.Mode=INP
PA1.Signal=COMP1_INP
PA10.GPIOParameters=GPIO_Label
PA10.GPIO_Label=PHC_H
PA10.Signal=S_TIM1_CH3
PA11.Mode=Device
PA11.Signal=USB_DM
PA12.Mode=Device
PA12.Signal=USB_DP
PA13.Mode=Trace_Asynchronous_SW
PA13.Signal=SYS_JTMS-SWDIO
PA14.Mode=Trace_Asynchronous_SW
PA14.Signal=SYS_JTCK-SWCLK
PA2.GPIOParameters=GPIO_Label
PA2.GPIO_Label=TEMP
PA2.Mode=IN3-Single-Ended
PA2.Signal=ADC1_IN3
PA4.GPIOParameters=GPIO_Label
PA4.GPIO_Label=PH_VNA
PA4.Mode=INM
PA4.Signal=COMP1_INM
PA5.GPIOParameters=GPIO_Label
PA5.GPIO_Label=PH_VNB
PA5.Mode=INM
PA5.Signal=COMP2_INM
PA7.GPIOParameters=GPIO_Label
PA7.GPIO_Label=PHB_FILT
PA7.Mode=INP
PA7.Signal=COMP2_INP
PA8.GPIOParameters=GPIO_Label
PA8.GPIO_Label=PHA_H
PA8.Signal=S_TIM1_CH1
PA9.GPIOParameters=GPIO_Label
PA9.GPIO_Label=PHB_H
PA9.Signal=S_TIM1_CH2
PB0.GPIOParameters=GPIO_Label
PB0.GPIO_Label=PHC_FILT
PB0.Mode=INP
PB0.Signal=COMP4_INP
PB13.GPIOParameters=GPIO_Label
PB13.GPIO_Label=PHA_L
PB13.Mode=PWM Generation1 CH1 CH1N
PB13.Signal=TIM1_CH1N
PB14.GPIOParameters=GPIO_Label
PB14.GPIO_Label=PHB_L
PB14.Mode=PWM Generation2 CH2 CH2N
PB14.Signal=TIM1_CH2N
PB15.GPIOParameters=GPIO_Label
PB15.GPIO_Label=PHC_L
PB15.Mode=PWM Generation3 CH3 CH3N
PB15.Signal=TIM1_CH3N
PB2.GPIOParameters=GPIO_Label
PB2.GPIO_Label=PH_VNC
PB2.Mode=INM
PB2.Signal=COMP4_INM
PB3.Mode=Trace_Asynchronous_SW
PB3.Signal=SYS_JTDO-SWO
PB5.Mode=FDCAN_Activate
PB5.Signal=FDCAN2_RX
PB6.Mode=FDCAN_Activate
PB6.Signal=FDCAN2_TX
PC13.GPIOParameters=PinState,GPIO_Label
PC13.GPIO_Label=LED1
PC13.PinState=GPIO_PIN_RESET
PC13.Signal=GPIO_Output
PC14-OSC32_IN.GPIOParameters=PinState,GPIO_Label
PC14-OSC32_IN.GPIO_Label=LED2
PC14-OSC32_IN.PinState=GPIO_PIN_RESET
PC14-OSC32_IN.Signal=GPIO_Output
PC15-OSC32_OUT.GPIOParameters=PinState,GPIO_Label
PC15-OSC32_OUT.GPIO_Label=LED3
PC15-OSC32_OUT.PinState=GPIO_PIN_RESET
PC15-OSC32_OUT.Signal=GPIO_Output
PF0-OSC_IN.Mode=HSE-External-Oscillator
PF0-OSC_IN.Signal=RCC_OSC_IN
PF1-OSC_OUT.Mode=HSE-External-Oscillator
PF1-OSC_OUT.Signal=RCC_OSC_OUT
RCC.HSE_VALUE=16000000
RCC.SYSCLKFreq_VALUE=170000000
RCC.SYSCLKSource=RCC_SYSCLKSOURCE_PLLCLK
board=custom

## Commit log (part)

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2024-09-13 init hardware and software folders. import current work
2024-09-14 update software mcu esc
2024-10-22 esc sensing circuitry
2024-10-22 update FCC stm32 ioc file
2024-10-23 update FCC bom
2024-10-23 add revision to FCC pdf, fix mcu boot option bytes, blink an LED!
2024-10-27 starting bmi driver...
2024-11-02 add GCS v1 and bmi088 driver
2024-12-03 add BMP388 press sensor driver, GCS rework to PyQT6
2024-12-15 add lis3mdl magnetometer driver
2024-12-15 update stm32 cubeide
2024-12-16 add hard iron calibration to magnetometer
2025-02-01 change drivers to C++, add software IIR filtering, improve GCS software
2025-02-01 improve IIR filter to second order Butterworth low pass
2025-02-17 adjust filter cutoff
2025-02-20 add orientation EKF git add .! using motion fx
2025-03-08 separation of logging into indep. thread, use threads flags, general refactor and optimization
2025-05-24 sensor fusion v1 !!!
2025-05-25 rest of the changes
2025-05-25 remove Debug/ folder, add .gitignore file
2025-05-25 add barometer filtering and complimentary filter validity check
2025-12-23 finish ESC hardware RevA, CC2500 driver working
2025-12-23 repo cleanup
2025-12-26 driver tuning
2025-12-26 gitignores and IIFiltering priming
2025-12-26 remove cache files
2025-12-27 sensor fusion tuning
2025-12-28 add leaky integrator to sensor fusion algorithm
2026-01-04 update docs
